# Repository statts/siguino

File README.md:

# Siguino

Low power board based on Arduino Pro Mini with in-built Sigfox network support

Siguino Eagle schematics, libraries and Arduino code created by Scott Tattersall

Further project info and manufactured boards for purchase at https://siguino.com

Detailed Getting Started Guide: https://siguino.com/step-by-step-guide/

3rd Party libraries / resources used:

Hardware:
- Many basic components (resistors, capacitors, etc) are from the SparkFun Eagle libraries
- LIS3DH accelerometer from SparkFun: https://github.com/sparkfun/SparkFun_LIS3DH_Arduino_Library
- Wisol Chip from hellogitty/WiSol (greatech.de) https://github.com/hellogitty/WiSOL

Software:
 (To install, go to url and "download zip", in Arduino IDE click Sketch->Include Library->Add zip and select downloaded zip file)
- LowPower library from RocketScream: https://github.com/rocketscream/Low-Power
- SparkFun LIS3DH library (https://github.com/sparkfun/SparkFun_LIS3DH_Arduino_Library)
- Arduino Sensors library (https://github.com/adafruit/Adafruit_Sensor)
- Arduino Bosch BME280 library (https://github.com/adafruit/Adafruit_BME280_Library)
- AltSoftSerial (https://github.com/PaulStoffregen/AltSoftSerial)

Enclosure:
- CAD (STL) files for sample enclosure that can be 3d printed as needed

# Sample projects
Along with the sigfox_sensors project that sends all sensor information here is another simple example project:

- Weather Station (arduino/weather_station)
Follow the same above software section to install the approriate libraries first, then download the weather station code.
The code can be flashed onto the Siguino via a standard FTDI breakout board (3.3v version only!), e.g. 
https://www.sparkfun.com/products/9873

The code: A simple weather station that sends avg temperature, light level, humidity and atmospheric pressure. If using Wia to process the data (see above getting started link), these can be easily graphed in Wia using a Wia Widget:
https://developers.wia.io/docs/add-a-widget

More information on integrating with Wia:
https://siguino.com/getting-started-with-siguino-and-wia-io/

Example:

")

# Eagle libraries
In eagle, set the directories for libraries to add the libary files included here if not already included, e.g.
$EAGLEDIR/lbr:{PROJECT-DIR}/Libraries/SparkFun-Eagle-Libraries-master:{PROJECT-DIR}/Libraries/WiSOL-master/Eagle_Library

Plus use the New Library -> execute script to add the components in script form from the scripts dir

# Hardware Revision History:

Rev 0.1: First version, trimmed board

Rev 0.2:
1) Add Reset Pin out as well as dtr for bootloading
2) Change C8 10uf format to standard 0603
3) Update routing to account for unsaved work
4) Re-write/tidy arduino sketch
5) Add de-coupling caps 10uf, 100nf to Accel chip VDD
6) Connect INT1 pin on Accel to D3

Rev 0.3:
1) Add Battery Holder
2) Add Reverse polarity Protection
3) Reposition Antenna

Rev 0.4:
1) Replace Temperature chip
2) Re-route temperature chip
3) Add registration hole for battery holder
4) Minor re-routing of vias under chips

Rev 0.5 / 1.0:
1) Added Magnetometer
2) Replaced temp chip with Temp & Pressure (Bosch BME 280)
3) Re-routing for manufacturing

Rev 1.1:
1) Improved Schematic (with thanks to Marnix Janse)
2) Improved Antenna trace (with thanks to Marnix Janse)

# Licence & Contact

Siguino Hardware and Software licenced under GPLv3, any questions or issues please contact scott@dock.ie

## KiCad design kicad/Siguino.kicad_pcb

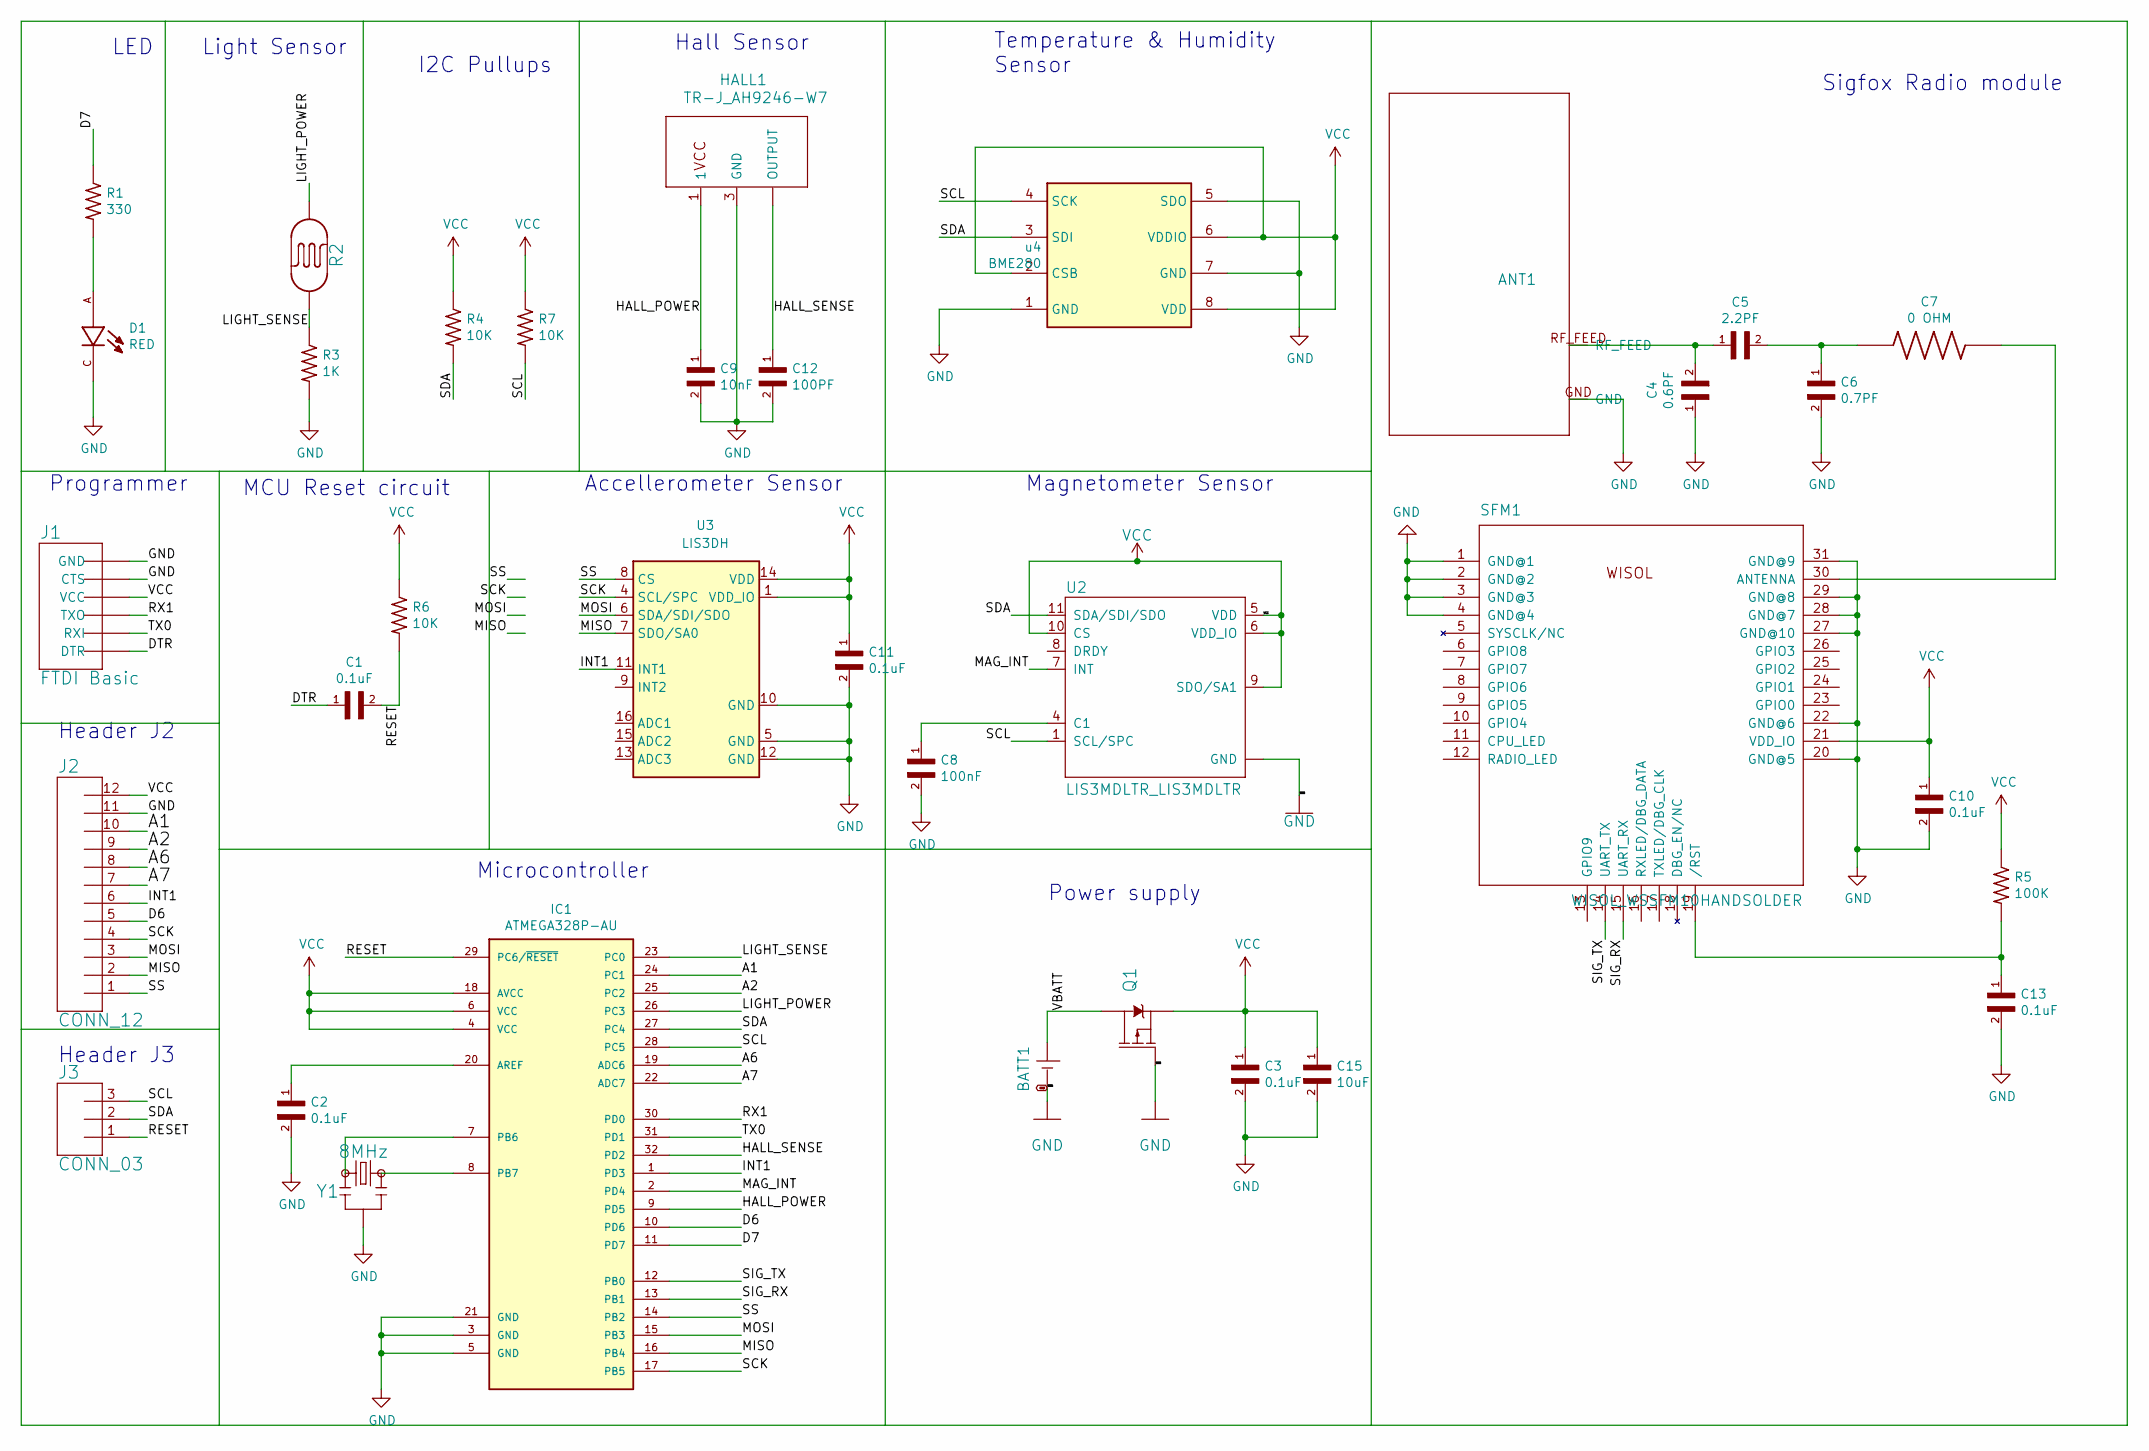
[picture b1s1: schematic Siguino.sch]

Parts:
ANT1: PROOB471; ONBOARD_SMD_2400
BATT1: SPARKFUN-BATTERIES_CR2-BATTERY-HOLDERPTH; SPARKFUN-BATTERIES_BATTERYHOLDER-CR2
C1, C2, C3, C10, C11, C13: 0.1uF; CAPC0603X33N
C4: 0.6PF; CAPC0402X22N
C5: 2.2PF; CAPC0402X22N
C6: 0.7PF; CAPC0402X22N
C7: 0 OHM; RESC1005X35N
C8: 100nF; CAPC0603X33N
C9: 10nF; CAPC0603X33N
C12: 100PF; CAPC0603X33N
C15: 10uF; CAPC0603X33N
D1: RED; LED_SML-D12Y1WT86
HALL1: TR-J_AH9246-W7; SC-59
IC1: ATMEGA328P-AU; QFP80P900X900X120-32N
J1: FTDI Basic; 1X06
J2: CONN_12; 1X12
J3: CONN_03; 1X03
Q1: MOSFET P-CH 20V 5.3A SOT-23; SOT23-3
R1: 330; RESC1608X50N; Tolerance .1%; Voltage_Rating 50 V
R2: PHOTOCELLPTH; PHOTOCELL
R3: 1K; RESC1608X50N; Tolerance .1%; Voltage_Rating 50 V
R4, R6, R7: 10K; RESC1608X50N; Tolerance .1%; Voltage_Rating 50 V
R5: 100K; RESC1608X50N; Tolerance .1%; Voltage_Rating 50 V
SFM1: WISOL_WSSFM10HANDSOLDER; WISOL_WSSFM10
U2: LIS3MDLTR_LIS3MDLTR; LIS3MDLTR_LGA12R50P4X4_200X200X100
U3: LIS3DH; LGA-16_3x3mm_P0.5mm_LayoutBorder3x5y
Y1: 8MHz; RESONATOR-SMD-3.2X1.3
u4: BME280; Bosch_LGA-8_2.5x2.5mm_P0.65mm_ClockwisePinNumbering

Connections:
/A1: IC1.24 (PC1), J2.10
/A2: IC1.25 (PC2), J2.9
/A6: IC1.19 (ADC6), J2.8
/A7: IC1.22 (ADC7), J2.7
/D6: IC1.10 (PD6), J2.5
/D7: IC1.11 (PD7), R1.1
/DTR: C1.1, J1.1 (DTR)
/HALL_POWER: C9.1, HALL1.1, IC1.9 (PD5)
/HALL_SENSE: C12.1, HALL1.2 (OUTPUT), IC1.32 (PD2)
/INT1: IC1.1 (PD3), J2.6, U3.11 (INT1)
/LIGHT_POWER: IC1.26 (PC3), R2.1
/LIGHT_SENSE: IC1.23 (PC0), R2.2, R3.1
/MAG_INT: IC1.2 (PD4), U2.7 (INT)
/MISO: IC1.16 (PB4), J2.2, U3.7 (SDO/SA0)
/MOSI: IC1.15 (PB3), J2.3, U3.6 (SDA/SDI/SDO)
/RESET: C1.2, IC1.29 (PC6/~RESET), J3.1, R6.2
/RX1: IC1.30 (PD0), J1.3 (TXO)
/SCK: IC1.17 (PB5), J2.4, U3.4 (SCL/SPC)
/SCL: IC1.28 (PC5), J3.3, R7.2, U2.1 (SCL/SPC), u4.4 (SCK)
/SDA: IC1.27 (PC4), J3.2, R4.2, U2.11 (SDA/SDI/SDO), u4.3 (SDI)
/SIG_RX: IC1.13 (PB1), SFM1.15 (UART_RX)
/SIG_TX: IC1.12 (PB0), SFM1.14 (UART_TX)
/SS: IC1.14 (PB2), J2.1, U3.8 (CS)
/TX0: IC1.31 (PD1), J1.2 (RXI)
/VBATT: BATT1.VBATT, Q1.3 (D)
GND: ANT1.GND, BATT1.GND, C2.2, C3.2, C4.1, C6.2, C8.2, C9.2, C10.2, C11.2, C12.2, C13.2, C15.2, D1.C, HALL1.3 (GND), IC1.3 (GND), IC1.5 (GND), IC1.21 (GND), J1.5 (CTS), J1.6 (GND), J2.11, Q1.1 (G), R3.2, SFM1.1 (GND@1), SFM1.2 (GND@2), SFM1.3 (GND@3), SFM1.4 (GND@4), SFM1.20 (GND@5), SFM1.22 (GND@6), SFM1.27 (GND@10), SFM1.28 (GND@7), SFM1.29 (GND@8), SFM1.31 (GND@9), U2.2 (GND), U2.3 (GND), U2.12 (GND), U3.5 (GND), U3.10 (GND), U3.12 (GND), Y1.2, u4.1 (GND), u4.5 (SDO), u4.7 (GND)
unnamed: ANT1.RF_FEED, C4.2, C5.1
unnamed: C2.1, IC1.20 (AREF)
unnamed: C5.2, C6.1, C7.1
unnamed: C7.2, SFM1.30 (ANTENNA)
unnamed: C8.1, U2.4 (C1)
unnamed: C13.1, R5.2, SFM1.19 (/RST)
unnamed: D1.A, R1.2
unnamed: IC1.7 (PB6), Y1.1
unnamed: IC1.8 (PB7), Y1.3
VCC: C3.1, C10.1, C11.1, C15.1, IC1.4 (VCC), IC1.6 (VCC), IC1.18 (AVCC), J1.4 (VCC), J2.12, Q1.2 (S), R4.1, R5.1, R6.1, R7.1, SFM1.21 (VDD_IO), U2.5 (VDD), U2.6 (VDD_IO), U2.9 (SDO/SA1), U2.10 (CS), U3.1 (VDD_IO), U3.14 (VDD), u4.2 (CSB), u4.6 (VDDIO), u4.8 (VDD)

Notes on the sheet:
Light Sensor
I2C Pullups
Hall Sensor
Temperature & Humidity Sensor
Magnetometer Sensor
Accellerometer Sensor
LED
MCU Reset circuit
Programmer
Header J2
Header J3
Microcontroller
Power supply
Sigfox Radio module

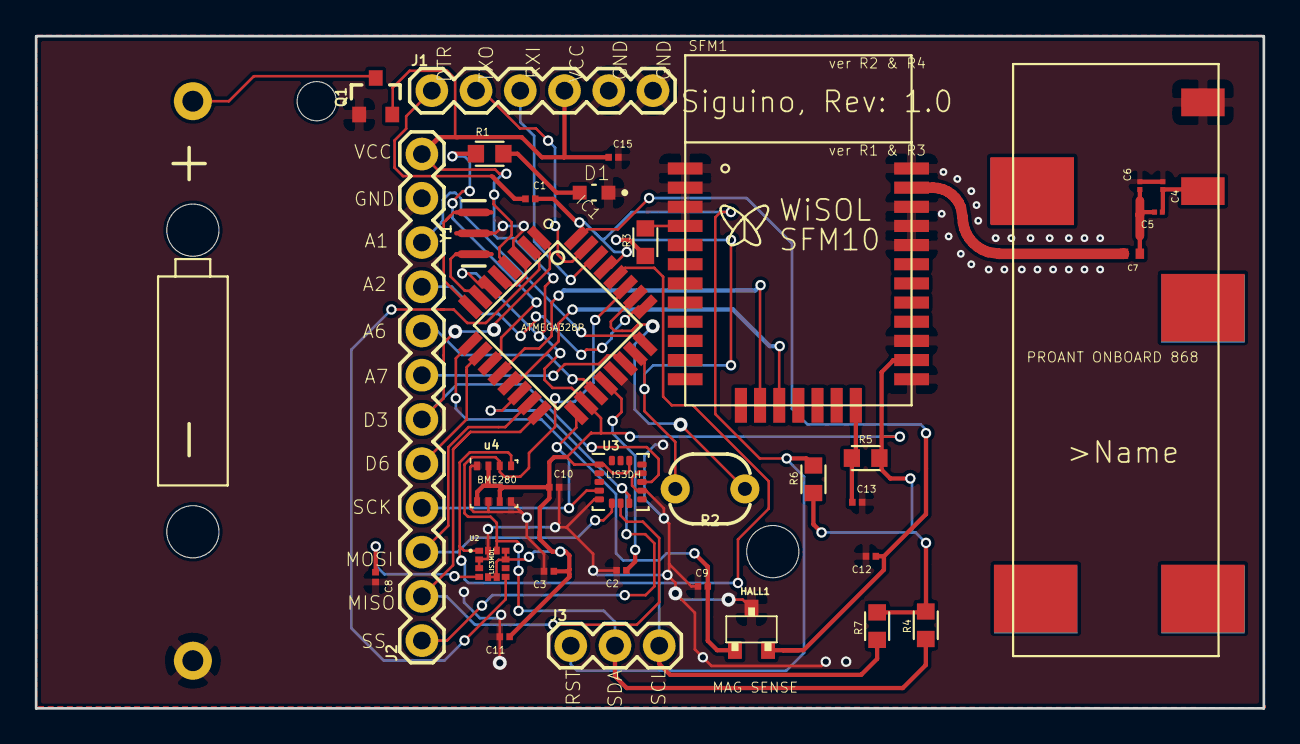
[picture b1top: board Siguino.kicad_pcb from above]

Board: 16 copper layers, 70.5 x 38.6 mm, 36 parts (0 on the bottom side), 36 nets.

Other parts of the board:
@HOLE0: (no value)

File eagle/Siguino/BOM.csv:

"Part";"Value";"Device";"Package";"Description";"DESCRIPTION";"DIGI-KEY_PART_NUMBER";"DIGI-KEY_PURCHASE_URL";"MF";"MP";"PACKAGE";"PROD_ID";"SF_ID";"VALUE";
"ANT1";"PROOB471";"PROANT_PRO-OB-471_ONBOARD";"PROANT_ONBOARD_SMD_868_915";"Proant OnBoard Antenna PRO-OB-471 for 868/915MHz comms (e.g. SigFox)";"";"";"";"";"";"";"";"";"";
"BATT1";"SPARKFUN-BATTERIES_CR2-BATTERY-HOLDERPTH";"SPARKFUN-BATTERIES_CR2-BATTERY-HOLDERPTH";"SPARKFUN-BATTERIES_BATTERYHOLDER-CR2";"CR2 Battery holder from MPD, see DigiKey product here:";"";"";"";"";"";"";"";"";"";
"C1";"0.1uF";"0.1UF-0603-25V-5%";"0603";"0.1µF ceramic capacitors";"";"";"";"";"";"";"CAP-08604";"";"0.1uF";
"C2";"0.1uF";"0.1UF-0603-25V-5%";"0603";"0.1µF ceramic capacitors";"";"";"";"";"";"";"CAP-08604";"";"0.1uF";
"C3";"0.1uF";"0.1UF-0603-25V-5%";"0603";"0.1µF ceramic capacitors";"";"";"";"";"";"";"CAP-08604";"";"0.1uF";
"C4";"0.6pF";"0.8PF-0402-50V-0.1PF";"0402";"0.8pF ceramic capacitors";"";"";"";"";"";"";"CAP-13456";"";"0.8pF";
"C5";"2.2pF";"0.8PF-0402-50V-0.1PF";"0402";"0.8pF ceramic capacitors";"";"";"";"";"";"";"CAP-13456";"";"0.8pF";
"C6";"0.7pF";"0.8PF-0402-50V-0.1PF";"0402";"0.8pF ceramic capacitors";"";"";"";"";"";"";"CAP-13456";"";"0.8pF";
"C7";" 0 OHM";"RESISTOR0402";"0402";"Generic Resistor Package";"";"";"";"";"";"";" ";"";" ";
"C8";"100nF";"0.1UF-0603-25V-5%";"0603";"0.1µF ceramic capacitors";"";"";"";"";"";"";"CAP-08604";"";"0.1uF";
"C9";"10nF";"10NF-0603-50V-10%";"0603";"0.01uF/10nF/10,000pF ceramic capacitors";"";"";"";"";"";"";"CAP-00867";"";"10nF";
"C10";"0.1uF";"0.1UF-0603-25V-(+80/-20%)";"0603";"0.1µF ceramic capacitors";"";"";"";"";"";"";"CAP-00810";"";"0.1uF";
"C11";"0.1uF";"0.1UF-0603-25V-5%";"0603";"0.1µF ceramic capacitors";"";"";"";"";"";"";"CAP-08604";"";"0.1uF";
"C12";"100pF";"100PF-0603-50V-5%";"0603";"100pF/0.1nF ceramic capacitors";"";"";"";"";"";"";"CAP-07883";"";"100pF";
"C13";"0.1uF";"0.1UF-0603-25V-(+80/-20%)";"0603";"0.1µF ceramic capacitors";"";"";"";"";"";"";"CAP-00810";"";"0.1uF";
"C15";"10uF";"10UF-0603-6.3V-20%";"0603";"10.0µF ceramic capacitors";"";"";"";"";"";"";"CAP-11015";"";"10uF";
"D1";"RED";"LED-RED0603";"LED-0603";"Red SMD LED";"";"";"";"";"";"";"DIO-00819";"";"RED";
"HALL1";"TR-J_AH9246-W7";"TR-J_AH9246-W7";"TR-J_SC-59";"Hall effect switch, surface mount, part number AH9246-W-7";"";"";"";"";"";"";"";"";"";
"J1";"FTDI Basic";"6_PIN_SERIAL_TARGET";"1X06";"6-pin header connection for use with the "FTDI BASIC" pinout - TARGET SIDE.";"";"";"";"";"";"";"";"";"";
"J2";"";"CONN_12";"1X12";"Multi connection point. Often used as Generic Header-pin footprint for 0.1 inch spaced/style header connections";"";"";"";"";"";"";"";"";"";
"J3";"";"CONN_03";"1X03";"Multi connection point. Often used as Generic Header-pin footprint for 0.1 inch spaced/style header connections";"";"";"";"";"";"";"";"";"";
"Q1";"MOSFET P-CH 20V 5.3A SOT-23";"MOSFET_PCHSI2323DDS";"SOT23-3";"P-channel MOSFETs";"";"";"";"";"";"";"SI2323DDS-T1-GE3";"";"MOSFET P-CH 20V 5.3A SOT-23";
"R1";"330";"330OHM-0603-1/10W-1%";"0603";"330Ω resistor";"";"";"";"";"";"";"RES-00818";"";"330";
"R2";"PHOTOCELLPTH";"PHOTOCELLPTH";"PHOTOCELL";"Photocell (Photodetector, Photo Resistor, CdS)";"";"";"";"";"";"";"COMP-09129";"SEN-09088";"";
"R3";"1k";"1KOHM-0603-1/10W-1%";"0603";"1kΩ resistor";"";"";"";"";"";"";"RES-07856";"";"1k";
"R4";"10k";"10KOHM-0603-1/10W-1%";"0603";"10kΩ resistor";"";"";"";"";"";"";"RES-00824";"";"10k";
"R5";"100k";"100KOHM-0603-1/10W-1%";"0603";"100kΩ resistor";"";"";"";"";"";"";"RES-07828";"";"100k";
"R6";"10k";"10KOHM-0603-1/10W-1%";"0603";"10kΩ resistor";"";"";"";"";"";"";"RES-00824";"";"10k";
"R7";"10k";"10KOHM-0603-1/10W-1%";"0603";"10kΩ resistor";"";"";"";"";"";"";"RES-00824";"";"10k";
"SFM1";"";"WISOL_WSSFM10HANDSOLDER";"WISOL_WSSFM10";"WiSOL WSSFM10 Sigfox Module with PCB Footprint to enable handsolder";"";"";"";"";"";"";"";"";"";
"U1";"ATMEGA328P_TQFP";"ATMEGA328P_TQFP";"TQFP32-08";"Popular 328P in QFP";"";"";"";"";"";"";"IC-09069";"";"ATMEGA328P_TQFP";
"U2";"LIS3MDLTR_LIS3MDLTR";"LIS3MDLTR_LIS3MDLTR";"LIS3MDLTR_LGA12R50P4X4_200X200X100";"LIS3MDL Series 3 Axis ±2/±8/±12/±16 g 3.6V High Performance Magnetometer LGA-12";"SENSOR MAGMTR I2C/SPI 12LGA";"497-13892-1-ND";"https://www.digikey.co.uk/product-detail/en/stmicroelectroni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";"STMicroelectronics";"LIS3MDLTR";"VFLGA-12 STMicroelectronics";"";"";"";
"U3";"SPARKFUN-SENSORS_LIS3DH";"SPARKFUN-SENSORS_LIS3DH";"SPARKFUN-SENSORS_LGA-16-3X3";"ST Microelectronics LIS3DH 3-Axis +/-2/4/8/16g SPI/I2C Accelerometer";"";"";"";"";"";"";"IC-13419";"N/A";"";
"U4";"BME280";"BME280COMPONENTLIBRARY_BME280";"BME280COMPONENTLIBRARY_BME280_LGA";"";"";"";"";"";"";"";"IC-13090";"";"BME280";
"Y1";"8MHz";"RESONATOR-8MHZSMD_3.2X1.3";"RESONATOR-SMD-3.2X1.3";"8MHz Resonator";"";"";"";"";"";"";"XTAL-08895";"";"8MHz";

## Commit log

2017-12-07 Update readme with links
2017-12-07 Update readme markdown
2018-05-29 Updated with latest 0.5 and 1.0 changes
2018-07-19 Updated library links and getting started guide
2018-07-22 Fixed bug with total counters being re-zeroed in loop
2018-07-31 Extended send period to 15 mins
2018-08-29 Added additional example project for weather station
2018-08-29 Updated readme with reference to new project
2018-08-30 Updated image for temperature chart in samle project
2018-08-30 Updated position of chart image
2018-08-30 Fixed positioning
2018-09-14 Updated with fix for US FCC rules and WISOL SFM10R2 chip
2018-09-14 Updated weather station to send every 15 mins
2018-11-02 Updated readme with Getting Started Guide link
2018-11-08 Cleaned schematic & changed antenna path on Board
2018-11-21 Updated board and schematic with ERC and DRC check approvals
2018-11-21 Added cad files for 3d printing enclosure
2018-11-21 Fixed enclosure images
2018-11-21 Fixed enclosure images sizes
2018-12-10 Updated BOM
2018-12-15 Added new components and re-organised board, unrouted
2018-12-16 Re-routed board, unfinished
2018-12-20 Finalised v2.0 and re-routed, gerbers created
2018-12-20 Dir tidy & added cam processor file used for v2 gerbers
2019-02-28 Fixed bit packing issue up to 64bits
2019-03-06 Fixed hatching issue on antenna pads, fixed FTDI problem
2019-03-12 Minor updates
2019-03-12 Moved components and resized board to fit box
2019-03-27 Fixed issue with hatching on antenna pads causing RF issues
2019-03-27 Repo cleanup and added gitignore
2019-05-22 Added PPTC over current protection
2019-05-23 Version text changed
2020-01-28 Various updates
2021-02-13 KiCad Siguino Version
    Updated .gitignore for specific kicad files and added a folder with schematic and pcb converted to KiCad
